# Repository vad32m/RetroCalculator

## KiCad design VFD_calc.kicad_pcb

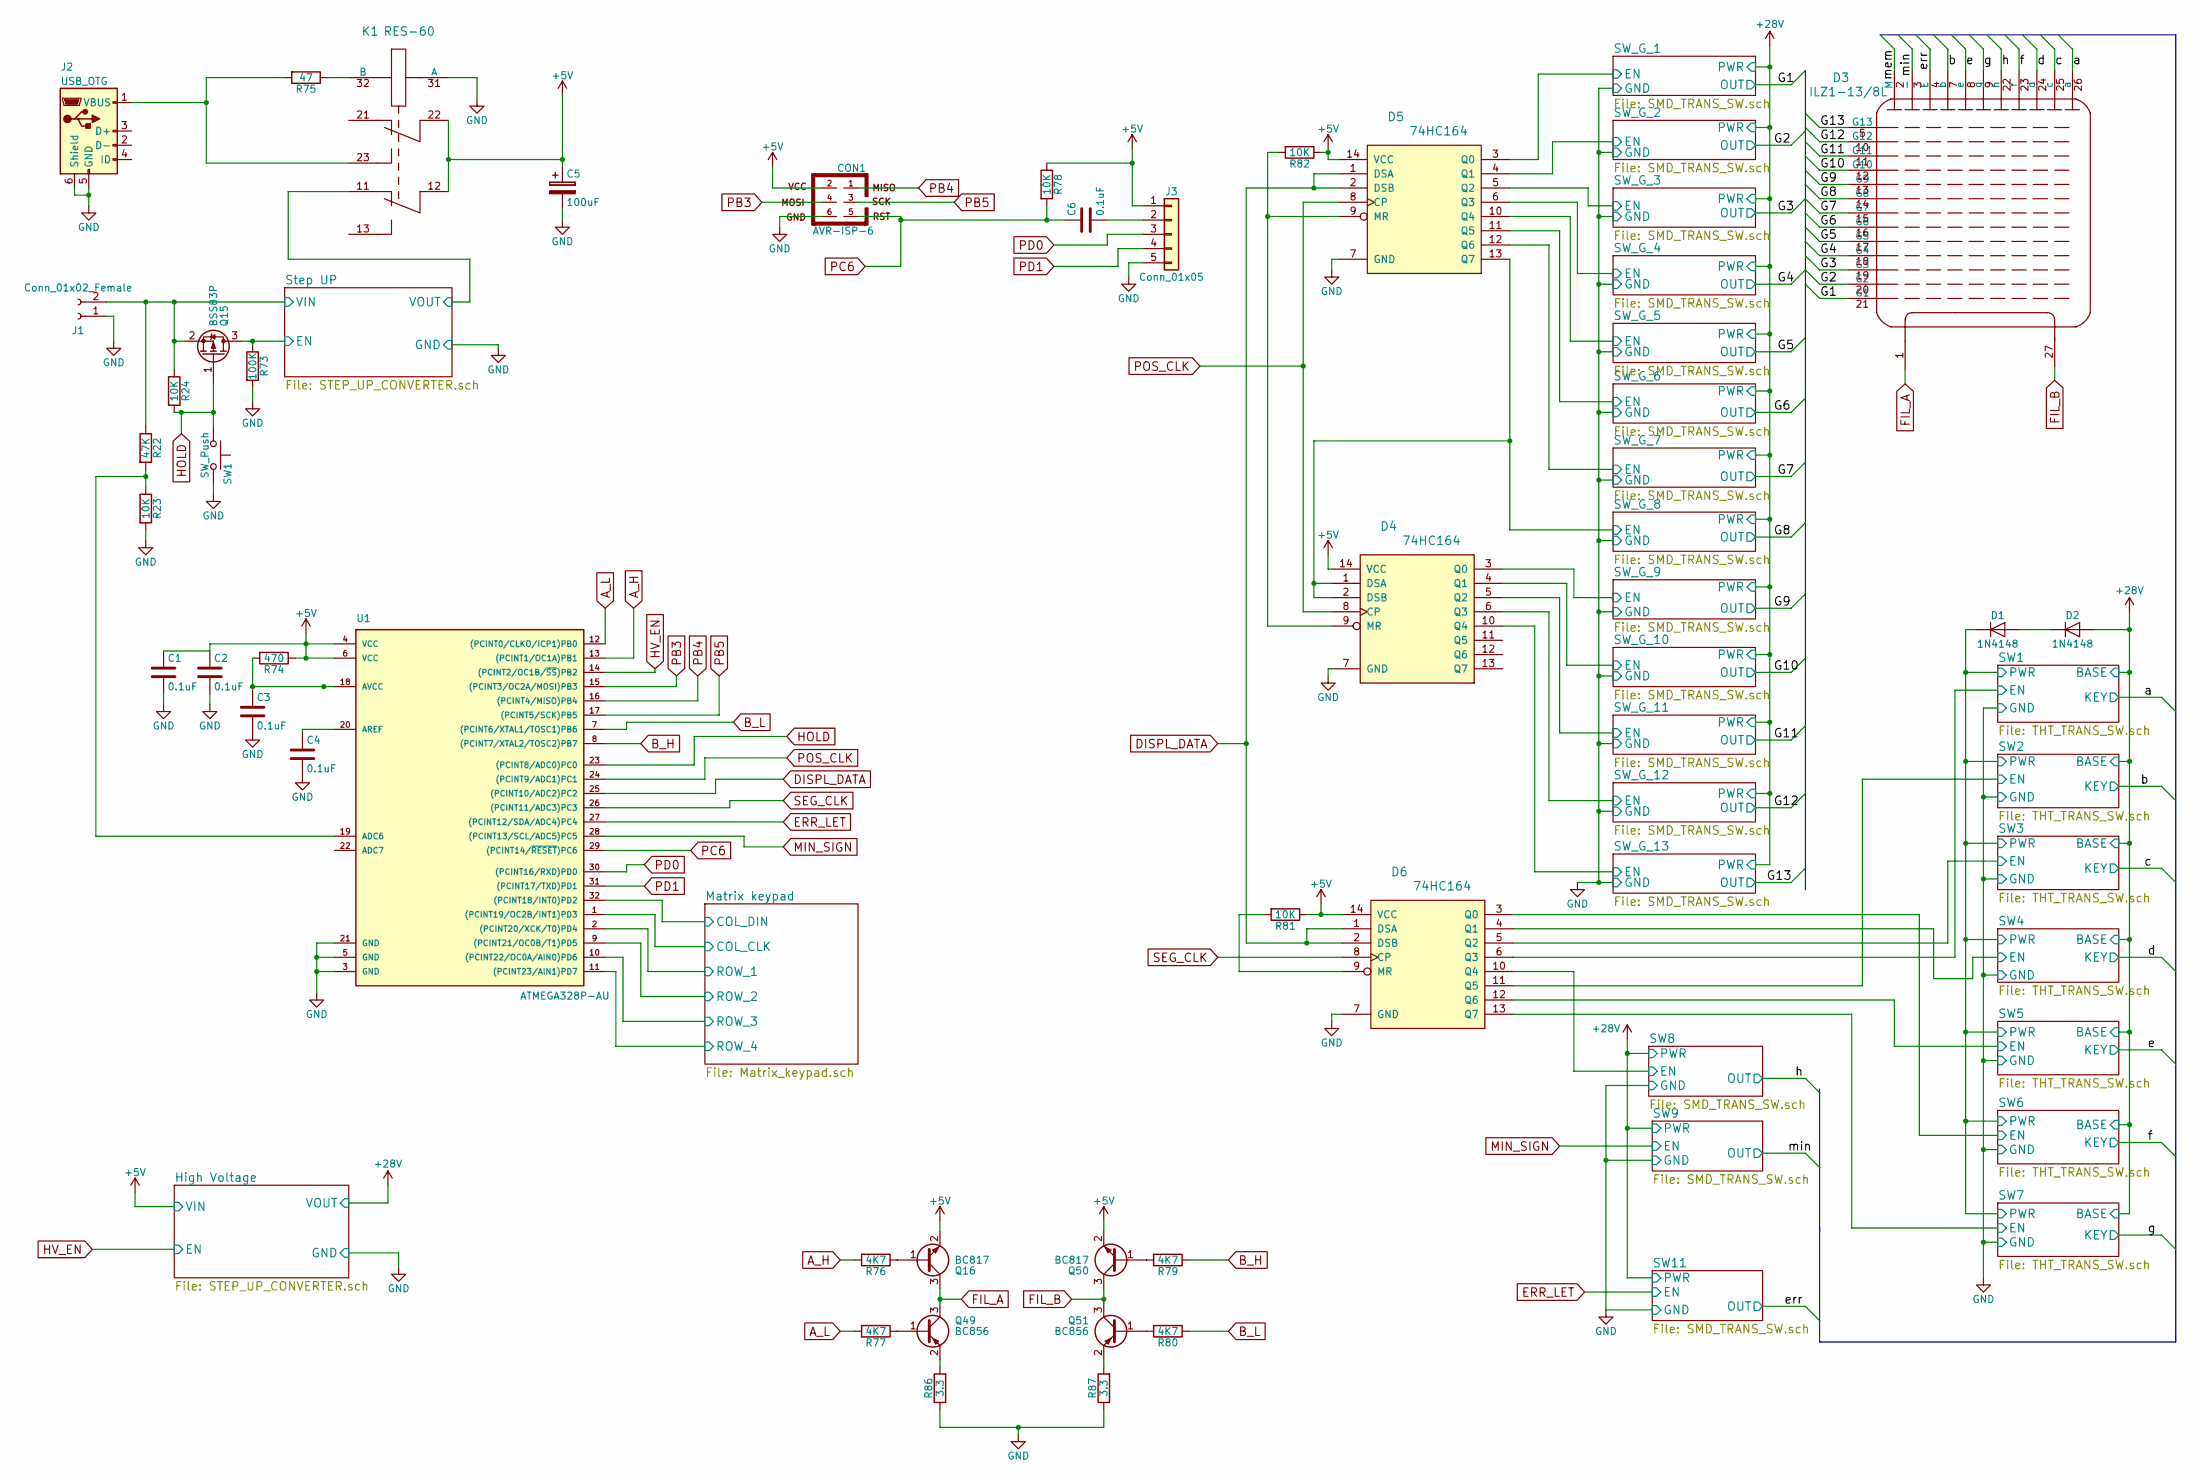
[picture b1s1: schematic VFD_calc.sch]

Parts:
C1, C2, C3, C4: 0.1uF; C_0805_HandSoldering
C5: 100uF; CP_Radial_D8.0mm_P2.50mm
C6: 0.1uF; R_0805_HandSoldering
CON1: AVR-ISP-6; Pin_Header_Straight_2x03_Pitch2.54mm
D1, D2: 1N4148; D_DO-35_SOD27_P10.16mm_Horizontal
D3: ILZ1-13/8L; ILZ1-13_8L
D4, D5, D6: 74HC164; SOIC-14_3.9x8.7mm_Pitch1.27mm
J1: Conn_01x02_Female; Socket_Strip_Angled_1x02_Pitch2.54mm
J2: USB_OTG; USB_Micro-B_Molex_47346-0001
J3: Conn_01x05; Pin_Header_Angled_1x05_Pitch2.54mm
K1: RES-60; RES_60
Q15: BSS83P; SOT-23
Q16, Q50: BC817; SOT-23
Q49, Q51: BC856; SOT-23
R22: 47K; R_0805_HandSoldering
R23, R24, R78, R81, R82: 10K; R_0805_HandSoldering
R73: 100K; R_0805_HandSoldering
R74: 470; R_0805_HandSoldering
R75: 47; R_0805_HandSoldering
R76, R77, R79, R80: 4K7; R_0805_HandSoldering
R86, R87: 3.3; R_0805_HandSoldering
SW1: SW_Push; SW_SPST_PTS645
U1: ATMEGA328P-AU; TQFP-32_7x7mm_Pitch0.8mm

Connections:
+5V: C1.1, C2.1, C5.1, CON1.2, D4.14 (VCC), D5.14 (VCC), D6.14 (VCC), J3.1, K1.12, K1.22, Q16.2 (E), Q50.2 (E), R74.1, R78.1, R81.1, R82.1, U1.4 (VCC), U1.6 (VCC); also elsewhere on the board
+28V: D2.2 (A); also elsewhere on the board
/G1: D3.21 (G1); also elsewhere on the board
/G2: D3.20 (G2); also elsewhere on the board
/G3: D3.19 (G3); also elsewhere on the board
/G4: D3.18 (G4); also elsewhere on the board
/G5: D3.17 (G5); also elsewhere on the board
/G6: D3.16 (G6); also elsewhere on the board
/G7: D3.15 (G7); also elsewhere on the board
/G8: D3.14 (G8); also elsewhere on the board
/G9: D3.13 (G9); also elsewhere on the board
/G10: D3.12 (G10); also elsewhere on the board
/G11: D3.11 (G11); also elsewhere on the board
/G12: D3.10 (G12); also elsewhere on the board
/G13: D3.5 (G13); also elsewhere on the board
/Matrix keypad/COL_CLK: U1.1 ((PCINT19/OC2B/INT1)PD3); also elsewhere on the board
/Matrix keypad/COL_DIN: U1.32 ((PCINT18/INT0)PD2); also elsewhere on the board
/Matrix keypad/ROW_1: U1.2 ((PCINT20/XCK/T0)PD4); also elsewhere on the board
/Matrix keypad/ROW_2: U1.9 ((PCINT21/OC0B/T1)PD5); also elsewhere on the board
/Matrix keypad/ROW_3: U1.10 ((PCINT22/OC0A/AIN0)PD6); also elsewhere on the board
/Matrix keypad/ROW_4: U1.11 ((PCINT23/AIN1)PD7); also elsewhere on the board
/SW1/EN: D6.6 (Q3); also elsewhere on the board
/SW1/PWR: D1.1 (K); also elsewhere on the board
/SW2/EN: D6.11 (Q5); also elsewhere on the board
/SW3/EN: D6.5 (Q2); also elsewhere on the board
/SW4/EN: D6.4 (Q1); also elsewhere on the board
/SW5/EN: D6.12 (Q6); also elsewhere on the board
/SW6/EN: D6.3 (Q0); also elsewhere on the board
/SW7/EN: D6.13 (Q7); also elsewhere on the board
/SW8/EN: D6.10 (Q4); also elsewhere on the board
/SW_G_1/EN: D5.3 (Q0); also elsewhere on the board
/SW_G_2/EN: D5.4 (Q1); also elsewhere on the board
/SW_G_3/EN: D5.5 (Q2); also elsewhere on the board
/SW_G_4/EN: D5.6 (Q3); also elsewhere on the board
/SW_G_5/EN: D5.10 (Q4); also elsewhere on the board
/SW_G_6/EN: D5.11 (Q5); also elsewhere on the board
/SW_G_7/EN: D5.12 (Q6); also elsewhere on the board
/SW_G_8/EN: D4.1 (DSA), D4.2 (DSB), D5.13 (Q7); also elsewhere on the board
/SW_G_9/EN: D4.3 (Q0); also elsewhere on the board
/SW_G_10/EN: D4.4 (Q1); also elsewhere on the board
/SW_G_11/EN: D4.5 (Q2); also elsewhere on the board
/SW_G_12/EN: D4.6 (Q3); also elsewhere on the board
/SW_G_13/EN: D4.10 (Q4); also elsewhere on the board
/Step UP/EN: Q15.3 (D), R73.1; also elsewhere on the board
/Step UP/VIN: J1.2, Q15.2 (S), R22.1, R24.1; also elsewhere on the board
/Step UP/VOUT: K1.11; also elsewhere on the board
/a: D3.26 (a); also elsewhere on the board
/b: D3.7 (b); also elsewhere on the board
/c: D3.25 (c); also elsewhere on the board
/d: D3.24 (d); also elsewhere on the board
/e: D3.8 (e); also elsewhere on the board
/err: D3.4 (E); also elsewhere on the board
/f: D3.23 (f); also elsewhere on the board
/g: D3.9 (g); also elsewhere on the board
/h: D3.22 (h); also elsewhere on the board
/mem: D3.2 (M)
/min: D3.3 (-); also elsewhere on the board
A_H: R76.2, U1.13 ((PCINT1/OC1A)PB1)
A_L: R77.2, U1.12 ((PCINT0/CLKO/ICP1)PB0)
B_H: R79.1, U1.8 ((PCINT7/XTAL2/TOSC2)PB7)
B_L: R80.1, U1.7 ((PCINT6/XTAL1/TOSC1)PB6)
DISPL_DATA: D5.1 (DSA), D5.2 (DSB), D6.1 (DSA), D6.2 (DSB), U1.25 ((PCINT10/ADC2)PC2)
ERR_LET: U1.27 ((PCINT12/SDA/ADC4)PC4); also elsewhere on the board
FIL_A: D3.1, Q16.3 (C), Q49.3 (C)
FIL_B: D3.27, Q50.3 (C), Q51.3 (C)
GND: C1.2, C2.2, C3.2, C4.2, C5.2, CON1.6, D4.7 (GND), D5.7 (GND), D6.7 (GND), J1.1, J2.5 (GND), J2.6 (Shield), J3.5, K1.31 (A), R23.2, R73.2, R86.1, R87.1, SW1.2, U1.3 (GND), U1.5 (GND), U1.21 (GND); also elsewhere on the board
HOLD: Q15.1 (G), R24.2, SW1.1, U1.23 ((PCINT8/ADC0)PC0)
HV_EN: U1.14 ((PCINT2/OC1B/~SS~)PB2); also elsewhere on the board
MIN_SIGN: U1.28 ((PCINT13/SCL/ADC5)PC5); also elsewhere on the board
unnamed: C3.1, R74.2, U1.18 (AVCC)
unnamed: C4.1, U1.20 (AREF)
unnamed: C6.2, J3.2
unnamed: D1.2 (A), D2.1 (K)
unnamed: D4.9 (MR), D5.9 (MR), R82.2
unnamed: D6.9 (MR), R81.2
unnamed: J2.1 (VBUS), K1.23, R75.2
unnamed: K1.32 (B), R75.1
unnamed: Q16.1 (B), R76.1
unnamed: Q49.1 (B), R77.1
unnamed: Q49.2 (E), R86.2
unnamed: Q50.1 (B), R79.2
unnamed: Q51.1 (B), R80.2
unnamed: Q51.2 (E), R87.2
unnamed: R22.2, R23.1, U1.19 (ADC6)
PB3: CON1.4, U1.15 ((PCINT3/OC2A/MOSI)PB3)
PB4: CON1.1, U1.16 ((PCINT4/MISO)PB4)
PB5: CON1.3, U1.17 ((PCINT5/SCK)PB5)
PC6: C6.1, CON1.5, R78.2, U1.29 ((PCINT14/~RESET~)PC6)
PD0: J3.3, U1.30 ((PCINT16/RXD)PD0)
PD1: J3.4, U1.31 ((PCINT17/TXD)PD1)
POS_CLK: D4.8 (CP), D5.8 (CP), U1.24 ((PCINT9/ADC1)PC1)
SEG_CLK: D6.8 (CP), U1.26 ((PCINT11/ADC3)PC3)

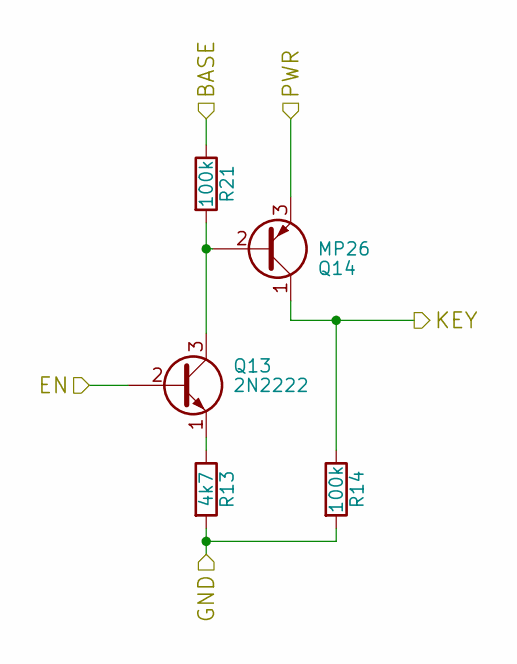
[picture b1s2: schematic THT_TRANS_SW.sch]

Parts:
Q1: 2N2222; TO-18-3
Q2: MP26; OldSowjetaera_Transistor_Type-II_BigPads
R1: 4k7; R_0805_HandSoldering
R2, R15: 100k; R_0805_HandSoldering

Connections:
+28V: R15.1; also elsewhere on the board
/SW1/EN: Q1.2 (B); also elsewhere on the board
/SW1/PWR: Q2.3 (E); also elsewhere on the board
/a: Q2.1 (C), R2.1; also elsewhere on the board
GND: R1.2, R2.2; also elsewhere on the board
unnamed: Q1.1 (E), R1.1
unnamed: Q1.3 (C), Q2.2 (B), R15.2

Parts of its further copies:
Q3, Q5, Q7, Q9, Q11, Q13: 2N2222; TO-18-3
Q4, Q6, Q8, Q10, Q12, Q14: MP26; OldSowjetaera_Transistor_Type-II_BigPads
R3, R5, R7, R9, R11, R13: 4k7; R_0805_HandSoldering
R4, R6, R8, R10, R12, R14, R16, R17, R18, R19, R20, R21: 100k; R_0805_HandSoldering

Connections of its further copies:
+28V: R16.1, R17.1, R18.1, R19.1, R20.1, R21.1; also elsewhere on the board
/SW1/PWR: Q4.3 (E), Q6.3 (E), Q8.3 (E), Q10.3 (E), Q12.3 (E), Q14.3 (E); also elsewhere on the board
/SW2/EN: Q3.2 (B); also elsewhere on the board
/SW3/EN: Q9.2 (B); also elsewhere on the board
/SW4/EN: Q13.2 (B); also elsewhere on the board
/SW5/EN: Q11.2 (B); also elsewhere on the board
/SW6/EN: Q7.2 (B); also elsewhere on the board
/SW7/EN: Q5.2 (B); also elsewhere on the board
/b: Q4.1 (C), R4.1; also elsewhere on the board
/c: Q10.1 (C), R10.1; also elsewhere on the board
/d: Q14.1 (C), R14.1; also elsewhere on the board
/e: Q12.1 (C), R12.1; also elsewhere on the board
/f: Q8.1 (C), R8.1; also elsewhere on the board
/g: Q6.1 (C), R6.1; also elsewhere on the board
GND: R3.2, R4.2, R5.2, R6.2, R7.2, R8.2, R9.2, R10.2, R11.2, R12.2, R13.2, R14.2; also elsewhere on the board
unnamed: Q3.1 (E), R3.1
unnamed: Q3.3 (C), Q4.2 (B), R16.2
unnamed: Q5.1 (E), R5.1
unnamed: Q5.3 (C), Q6.2 (B), R17.2
unnamed: Q7.1 (E), R7.1
unnamed: Q7.3 (C), Q8.2 (B), R18.2
unnamed: Q9.1 (E), R9.1
unnamed: Q9.3 (C), Q10.2 (B), R19.2
unnamed: Q11.1 (E), R11.1
unnamed: Q11.3 (C), Q12.2 (B), R20.2
unnamed: Q13.1 (E), R13.1
unnamed: Q13.3 (C), Q14.2 (B), R21.2

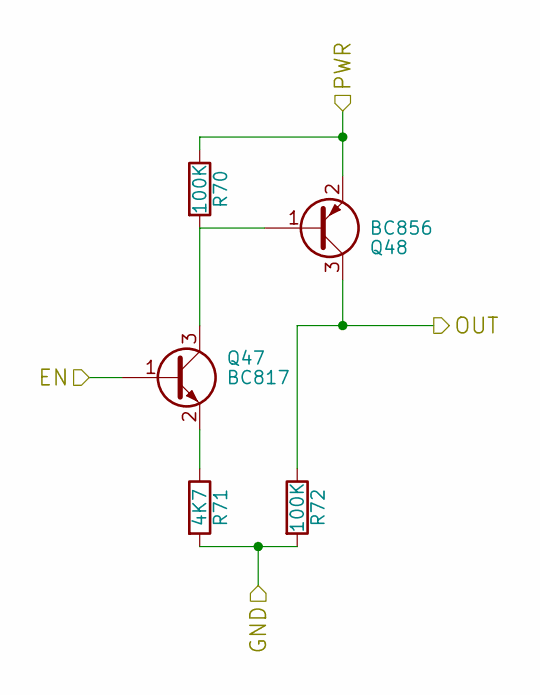
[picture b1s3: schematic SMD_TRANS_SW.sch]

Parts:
Q45: BC817; SOT-23
Q46: BC856; SOT-23
R67, R69: 100K; R_0805_HandSoldering
R68: 4K7; R_0805_HandSoldering

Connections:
+28V: Q46.2 (E), R67.1; also elsewhere on the board
/SW8/EN: Q45.1 (B); also elsewhere on the board
/h: Q46.3 (C), R69.1; also elsewhere on the board
GND: R68.2, R69.2; also elsewhere on the board
unnamed: Q45.2 (E), R68.1
unnamed: Q45.3 (C), Q46.1 (B), R67.2

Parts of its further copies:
Q17, Q19, Q21, Q23, Q25, Q27, Q29, Q31, Q33, Q35, Q37, Q39, Q41, Q43, Q47: BC817; SOT-23
Q18, Q20, Q22, Q24, Q26, Q28, Q30, Q32, Q34, Q36, Q38, Q40, Q42, Q44, Q48: BC856; SOT-23
R25, R27, R28, R30, R31, R33, R34, R36, R37, R39, R40, R42, R43, R45, R46, R48, R49, R51, R52, R54, R55, R57, R58, R60, R61, R63, R64, R66, R70, R72: 100K; R_0805_HandSoldering
R26, R29, R32, R35, R38, R41, R44, R47, R50, R53, R56, R59, R62, R65, R71: 4K7; R_0805_HandSoldering

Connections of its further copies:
+28V: Q18.2 (E), Q20.2 (E), Q22.2 (E), Q24.2 (E), Q26.2 (E), Q28.2 (E), Q30.2 (E), Q32.2 (E), Q34.2 (E), Q36.2 (E), Q38.2 (E), Q40.2 (E), Q42.2 (E), Q44.2 (E), Q48.2 (E), R25.1, R28.1, R31.1, R34.1, R37.1, R40.1, R43.1, R46.1, R49.1, R52.1, R55.1, R58.1, R61.1, R64.1, R70.1; also elsewhere on the board
/G1: Q20.3 (C), R30.1; also elsewhere on the board
/G2: Q28.3 (C), R42.1; also elsewhere on the board
/G3: Q32.3 (C), R48.1; also elsewhere on the board
/G4: Q26.3 (C), R39.1; also elsewhere on the board
/G5: Q42.3 (C), R63.1; also elsewhere on the board
/G6: Q24.3 (C), R36.1; also elsewhere on the board
/G7: Q48.3 (C), R72.1; also elsewhere on the board
/G8: Q38.3 (C), R57.1; also elsewhere on the board
/G9: Q40.3 (C), R60.1; also elsewhere on the board
/G10: Q36.3 (C), R54.1; also elsewhere on the board
/G11: Q34.3 (C), R51.1; also elsewhere on the board
/G12: Q30.3 (C), R45.1; also elsewhere on the board
/G13: Q22.3 (C), R33.1; also elsewhere on the board
/SW_G_1/EN: Q19.1 (B); also elsewhere on the board
/SW_G_2/EN: Q27.1 (B); also elsewhere on the board
/SW_G_3/EN: Q31.1 (B); also elsewhere on the board
/SW_G_4/EN: Q25.1 (B); also elsewhere on the board
/SW_G_5/EN: Q41.1 (B); also elsewhere on the board
/SW_G_6/EN: Q23.1 (B); also elsewhere on the board
/SW_G_7/EN: Q47.1 (B); also elsewhere on the board
/SW_G_8/EN: Q37.1 (B); also elsewhere on the board
/SW_G_9/EN: Q39.1 (B); also elsewhere on the board
/SW_G_10/EN: Q35.1 (B); also elsewhere on the board
/SW_G_11/EN: Q33.1 (B); also elsewhere on the board
/SW_G_12/EN: Q29.1 (B); also elsewhere on the board
/SW_G_13/EN: Q21.1 (B); also elsewhere on the board
/err: Q18.3 (C), R27.1; also elsewhere on the board
/min: Q44.3 (C), R66.1; also elsewhere on the board
ERR_LET: Q17.1 (B); also elsewhere on the board
GND: R26.2, R27.2, R29.2, R30.2, R32.2, R33.2, R35.2, R36.2, R38.2, R39.2, R41.2, R42.2, R44.2, R45.2, R47.2, R48.2, R50.2, R51.2, R53.2, R54.2, R56.2, R57.2, R59.2, R60.2, R62.2, R63.2, R65.2, R66.2, R71.2, R72.2; also elsewhere on the board
MIN_SIGN: Q43.1 (B); also elsewhere on the board
unnamed: Q17.2 (E), R26.1
unnamed: Q17.3 (C), Q18.1 (B), R25.2
unnamed: Q19.2 (E), R29.1
unnamed: Q19.3 (C), Q20.1 (B), R28.2
unnamed: Q21.2 (E), R32.1
unnamed: Q21.3 (C), Q22.1 (B), R31.2
unnamed: Q23.2 (E), R35.1
unnamed: Q23.3 (C), Q24.1 (B), R34.2
unnamed: Q25.2 (E), R38.1
unnamed: Q25.3 (C), Q26.1 (B), R37.2
unnamed: Q27.2 (E), R41.1
unnamed: Q27.3 (C), Q28.1 (B), R40.2
unnamed: Q29.2 (E), R44.1
unnamed: Q29.3 (C), Q30.1 (B), R43.2
unnamed: Q31.2 (E), R47.1
unnamed: Q31.3 (C), Q32.1 (B), R46.2
unnamed: Q33.2 (E), R50.1
unnamed: Q33.3 (C), Q34.1 (B), R49.2
unnamed: Q35.2 (E), R53.1
unnamed: Q35.3 (C), Q36.1 (B), R52.2
unnamed: Q37.2 (E), R56.1
unnamed: Q37.3 (C), Q38.1 (B), R55.2
unnamed: Q39.2 (E), R59.1
unnamed: Q39.3 (C), Q40.1 (B), R58.2
unnamed: Q41.2 (E), R62.1
unnamed: Q41.3 (C), Q42.1 (B), R61.2
unnamed: Q43.2 (E), R65.1
unnamed: Q43.3 (C), Q44.1 (B), R64.2
unnamed: Q47.2 (E), R71.1
unnamed: Q47.3 (C), Q48.1 (B), R70.2

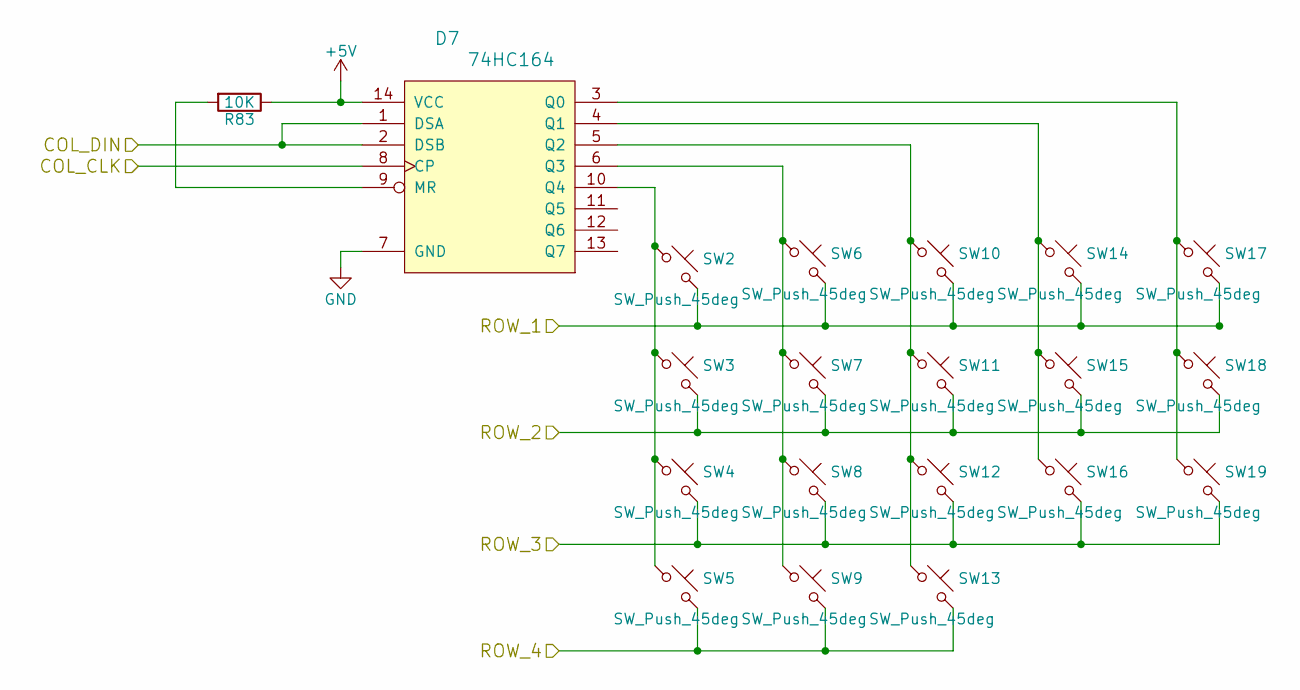
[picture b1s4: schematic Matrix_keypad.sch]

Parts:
D7: 74HC164; SOIC-14_3.9x8.7mm_Pitch1.27mm
R83: 10K; R_0805_HandSoldering
SW2, SW3, SW4, SW5, SW6, SW7, SW8, SW9, SW10, SW11, SW12, SW13, SW14, SW15, SW16, SW17, SW18, SW19: SW_Push_45deg; SW_SPST_PTS645

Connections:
+5V: D7.14 (VCC), R83.1; also elsewhere on the board
/Matrix keypad/COL_CLK: D7.8 (CP); also elsewhere on the board
/Matrix keypad/COL_DIN: D7.1 (DSA), D7.2 (DSB); also elsewhere on the board
/Matrix keypad/ROW_1: SW2.2, SW6.2, SW10.2, SW14.2, SW17.2; also elsewhere on the board
/Matrix keypad/ROW_2: SW3.2, SW7.2, SW11.2, SW15.2, SW18.2; also elsewhere on the board
/Matrix keypad/ROW_3: SW4.2, SW8.2, SW12.2, SW16.2, SW19.2; also elsewhere on the board
/Matrix keypad/ROW_4: SW5.2, SW9.2, SW13.2; also elsewhere on the board
GND: D7.7 (GND); also elsewhere on the board
unnamed: D7.3 (Q0), SW17.1, SW18.1, SW19.1
unnamed: D7.4 (Q1), SW14.1, SW15.1, SW16.1
unnamed: D7.5 (Q2), SW10.1, SW11.1, SW12.1, SW13.1
unnamed: D7.6 (Q3), SW6.1, SW7.1, SW8.1, SW9.1
unnamed: D7.9 (MR), R83.2
unnamed: D7.10 (Q4), SW2.1, SW3.1, SW4.1, SW5.1

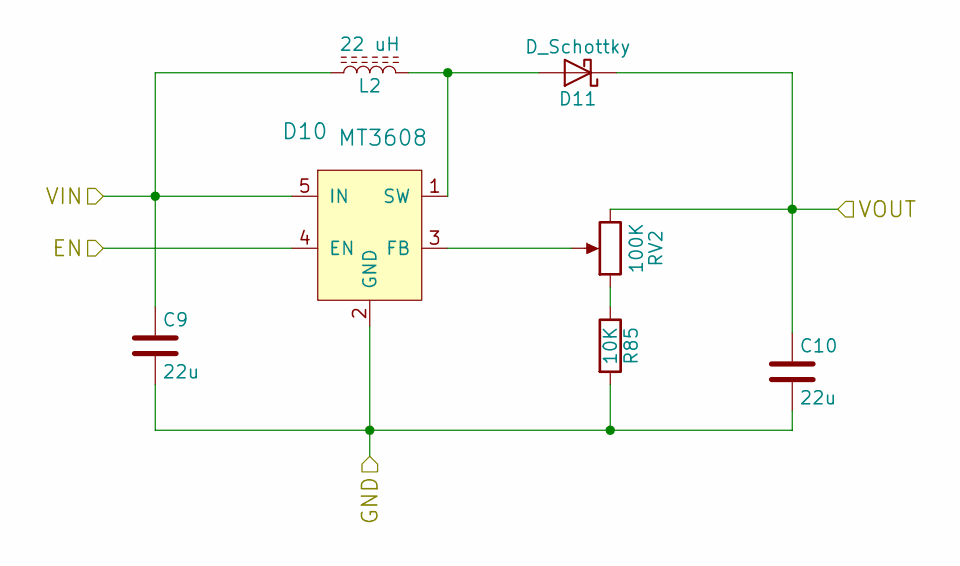
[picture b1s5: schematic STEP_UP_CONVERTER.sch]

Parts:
C7, C8: 22u; C_1210_HandSoldering
D8: MT3608; SOT-23-6_Handsoldering
D9: D_Schottky; D_SMC_Handsoldering
L1: 22 uH; L_Vishay_IHLP-4040
R84: 10K; R_0805
RV1: 100K; Potentiometer_Trimmer_Bourns_3339H_Horizontal

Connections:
/Step UP/EN: D8.4 (EN); also elsewhere on the board
/Step UP/VIN: C7.1, D8.5 (IN), L1.1; also elsewhere on the board
/Step UP/VOUT: C8.1, D9.1 (K), RV1.3; also elsewhere on the board
GND: C7.2, C8.2, D8.2 (GND), R84.2; also elsewhere on the board
unnamed: D8.1 (SW), D9.2 (A), L1.2
unnamed: D8.3 (FB), RV1.2
unnamed: R84.1, RV1.1

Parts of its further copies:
C9, C10: 22u; C_1210_HandSoldering
D10: MT3608; SOT-23-6_Handsoldering
D11: D_Schottky; D_SMC_Handsoldering
L2: 22 uH; L_Vishay_IHLP-4040
R85: 10K; R_0805
RV2: 100K; Potentiometer_Trimmer_Bourns_3339H_Horizontal

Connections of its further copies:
+5V: C9.1, D10.5 (IN), L2.1; also elsewhere on the board
+28V: C10.1, D11.1 (K), RV2.3; also elsewhere on the board
GND: C9.2, C10.2, D10.2 (GND), R85.2; also elsewhere on the board
HV_EN: D10.4 (EN); also elsewhere on the board
unnamed: D10.1 (SW), D11.2 (A), L2.2
unnamed: D10.3 (FB), RV2.2
unnamed: R85.1, RV2.1

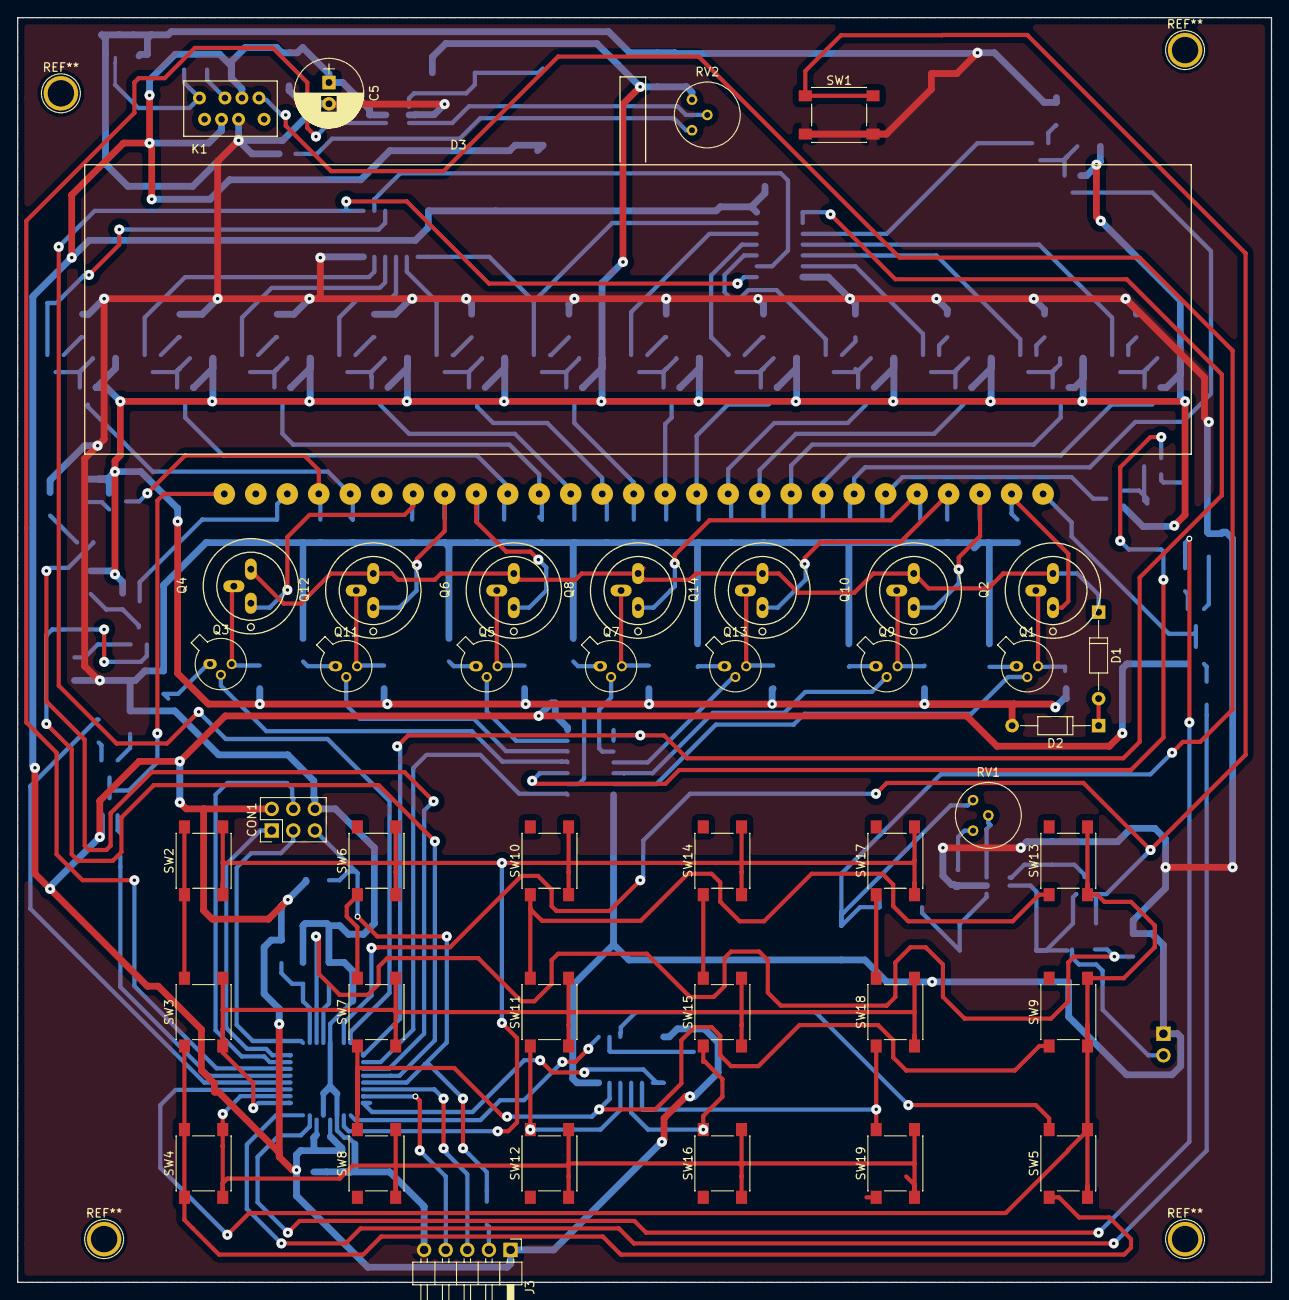
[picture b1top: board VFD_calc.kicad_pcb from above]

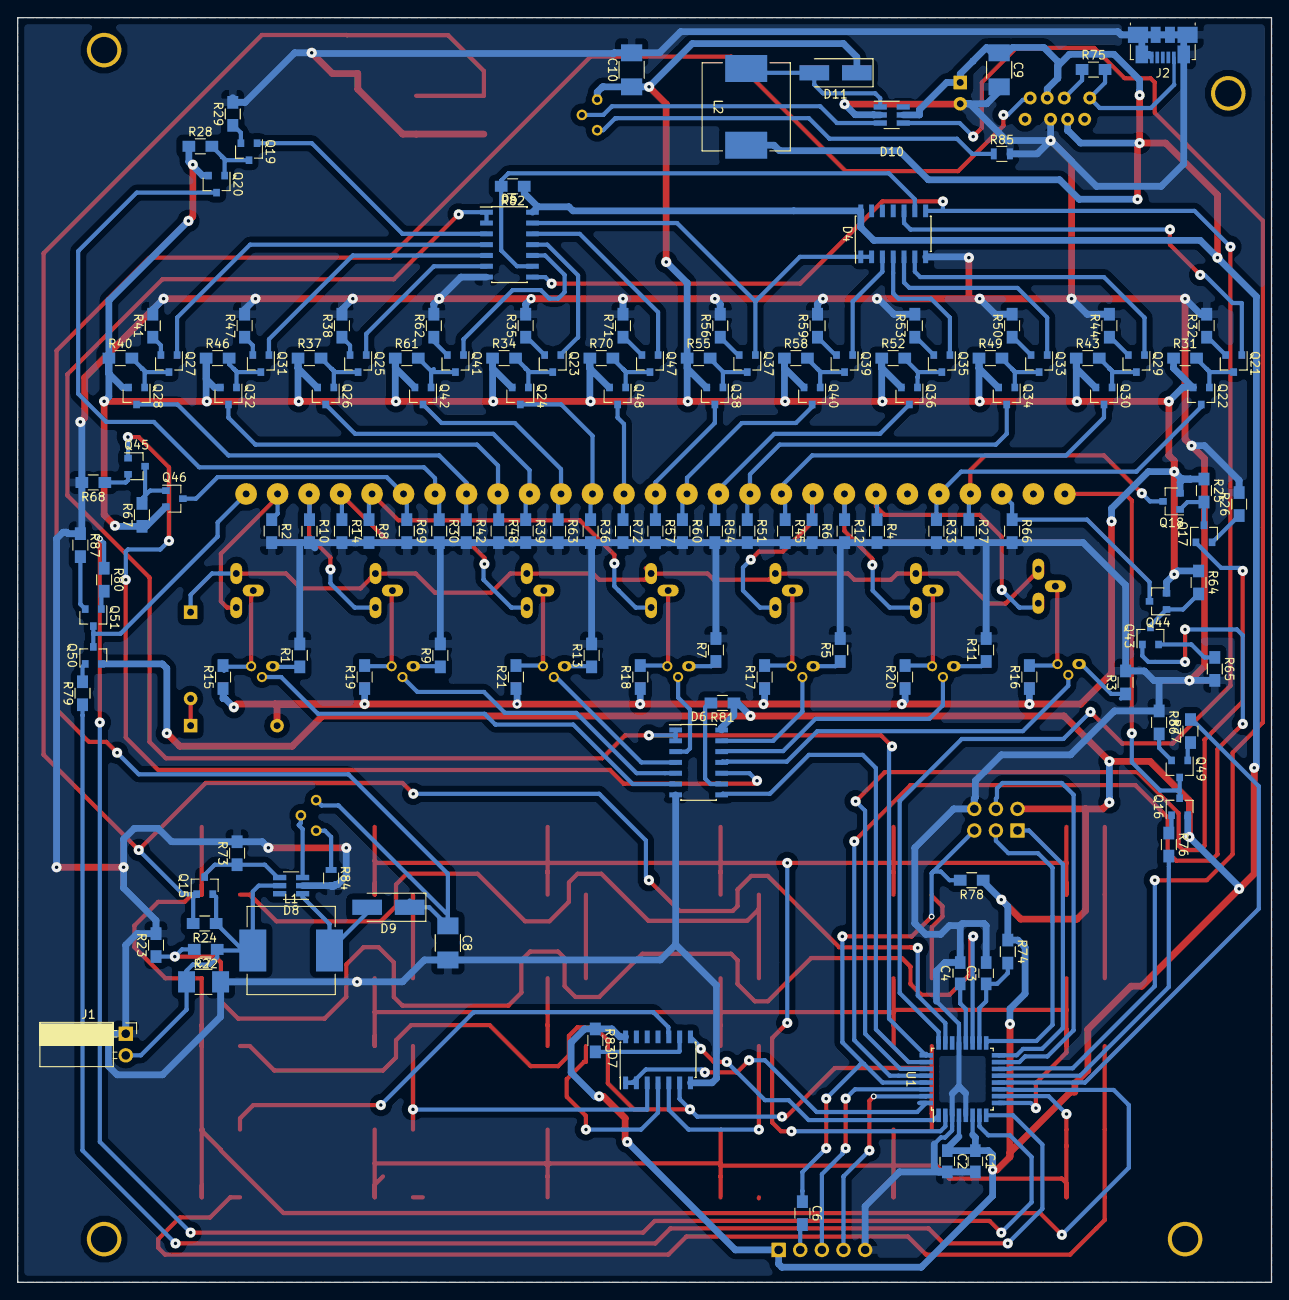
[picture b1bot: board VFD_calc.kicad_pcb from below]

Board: 2 copper layers, 147.3 x 148.6 mm, 188 parts (146 on the bottom side), 149 nets.

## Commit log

2018-03-04 Added gitignore file
2018-03-04 Added kicad project
2018-03-04 Minor cleanup
2018-03-14 Modified board layout (stil awful), so now it is more compact
2018-03-14 Increased vias, generated pdfs
